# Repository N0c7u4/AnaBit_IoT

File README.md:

# AnaBit IoT

# Wiki

La Wiki de AnaBit es un recurso invaluable que proporciona una amplia gama de información y guías prácticas para aprovechar al máximo esta tarjeta de desarrollo IoT. Al explorar la Wiki, encontraras una gran cantidad de contenido útil y relevante que les permitirá utilizar AnaBit en diversos proyectos. Algunos de los elementos que pueden encontrar en la Wiki incluyen:

-   `Documentación detallada`: La Wiki proporciona una documentación exhaustiva sobre AnaBit, incluyendo especificaciones técnicas, diagramas, esquemas y descripciones de los componentes. Esta información es fundamental para comprender las características y capacidades de la tarjeta.

-   `Guías de configuración`: La Wiki ofrece guías paso a paso para configurar correctamente AnaBit y establecer conexiones con diferentes protocolos de comunicación, como LoRa, Sigfox, Zigbee, WiFi y Bluetooth. Estas guías ayudan a iniciar rápidamente sus proyectos y asegurarse de que la tarjeta esté configurada correctamente.

-   `Tutoriales y ejemplos`: La Wiki contiene tutoriales prácticos que ilustran cómo utilizar AnaBit en diferentes escenarios y aplicaciones. Estos tutoriales incluyen ejemplos de código, configuraciones y diagramas de conexión, lo que facilita la comprensión de los conceptos y el aprendizaje práctico.

-   `Solución de problemas`: En caso de enfrentar dificultades o problemas durante el desarrollo con AnaBit, la Wiki ofrece secciones dedicadas a la resolución de problemas comunes. Estas secciones proporcionan consejos, trucos y posibles soluciones para superar obstáculos técnicos y maximizar la eficiencia en el desarrollo.

-   `Comunidad y recursos adicionales`: Además de la información técnica, la Wiki también puede servir como un punto de encuentro para la comunidad de AnaBit. Se pueden encontrar enlaces a foros de discusión, grupos de usuarios y otros recursos relacionados, lo que permite compartir conocimientos, colaborar e intercambiar ideas con otros entusiastas y expertos en IoT.

la pagina de la Wiki de AnaBit se aloja en el siguiente link:

[Wiki AnaBit](https://anabit-iot.readthedocs.io/es/latest/)

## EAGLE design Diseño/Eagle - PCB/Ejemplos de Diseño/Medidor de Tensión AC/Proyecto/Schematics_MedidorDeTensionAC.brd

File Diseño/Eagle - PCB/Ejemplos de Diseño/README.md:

# Proyectos Ejemplo EAGLE 9.0.0

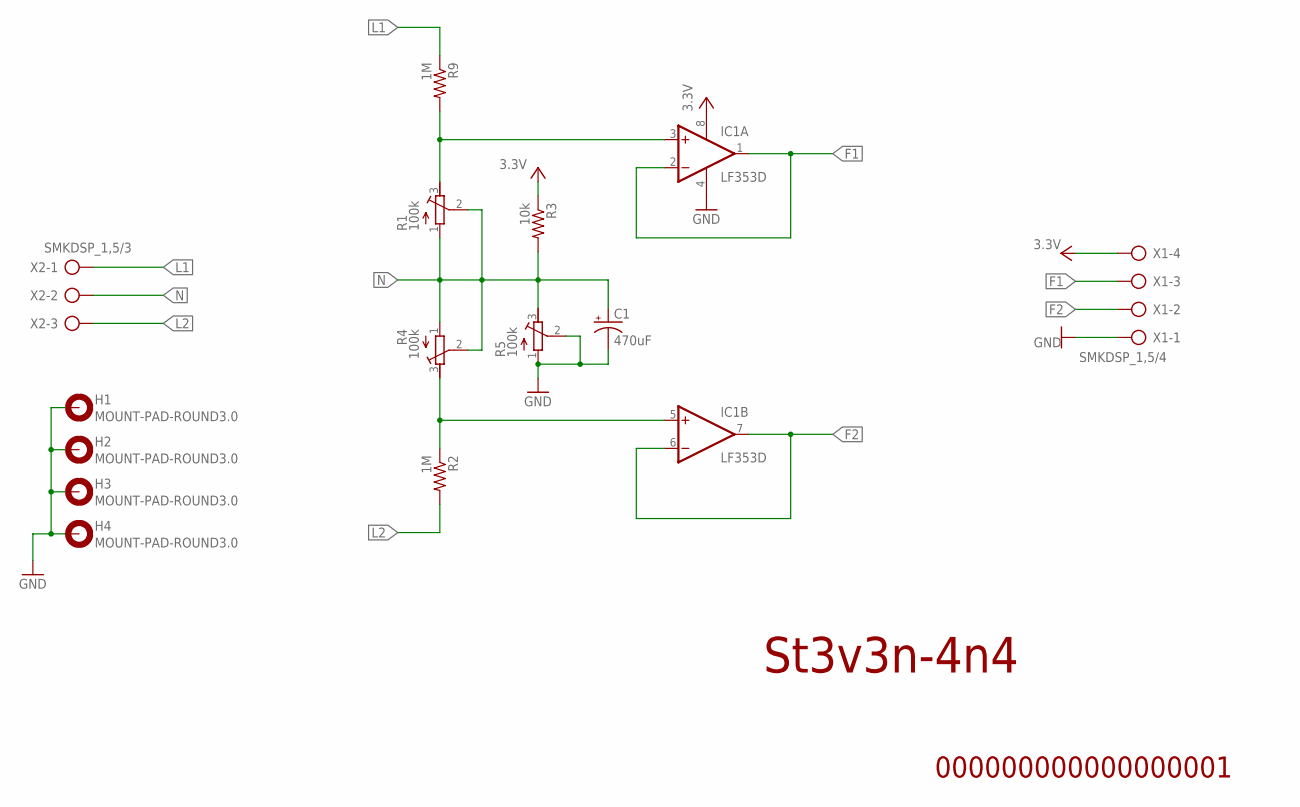
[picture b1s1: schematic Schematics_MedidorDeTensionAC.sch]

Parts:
C1: 470uF; E3,5-8
H1, H2, H3, H4: MOUNT-PAD-ROUND3.0; 3,0-PAD
IC1: LF353D; SO08
R1, R4, R5: 100k; RTRIM64W
R2, R9: 1M; 0207/10
R3: 10k; 0207/10
X1: SMKDSP_1,5/4
X2: SMKDSP_1,5/3

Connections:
F1: IC1.1 (OUT), IC1.2 (-IN), X1.3
F2: IC1.6 (-IN), IC1.7 (OUT), X1.2
GND: C1.-, H1.B3,0, H2.B3,0, H3.B3,0, H4.B3,0, IC1.4 (V-), R5.1 (A), R5.2 (S), X1.1
IN1+: IC1.3 (+IN), R1.3 (E), R9.2
L1: R9.1, X2.1
L2: R2.2, X2.3
N: C1.+, R1.1 (A), R1.2 (S), R3.2, R4.1 (A), R4.2 (S), R5.3 (E), X2.2
unnamed: IC1.5 (+IN), R2.1, R4.3 (E)
VCC: IC1.8 (V+), R3.1, X1.4

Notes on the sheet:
000000000000000001
St3v3n-4n4

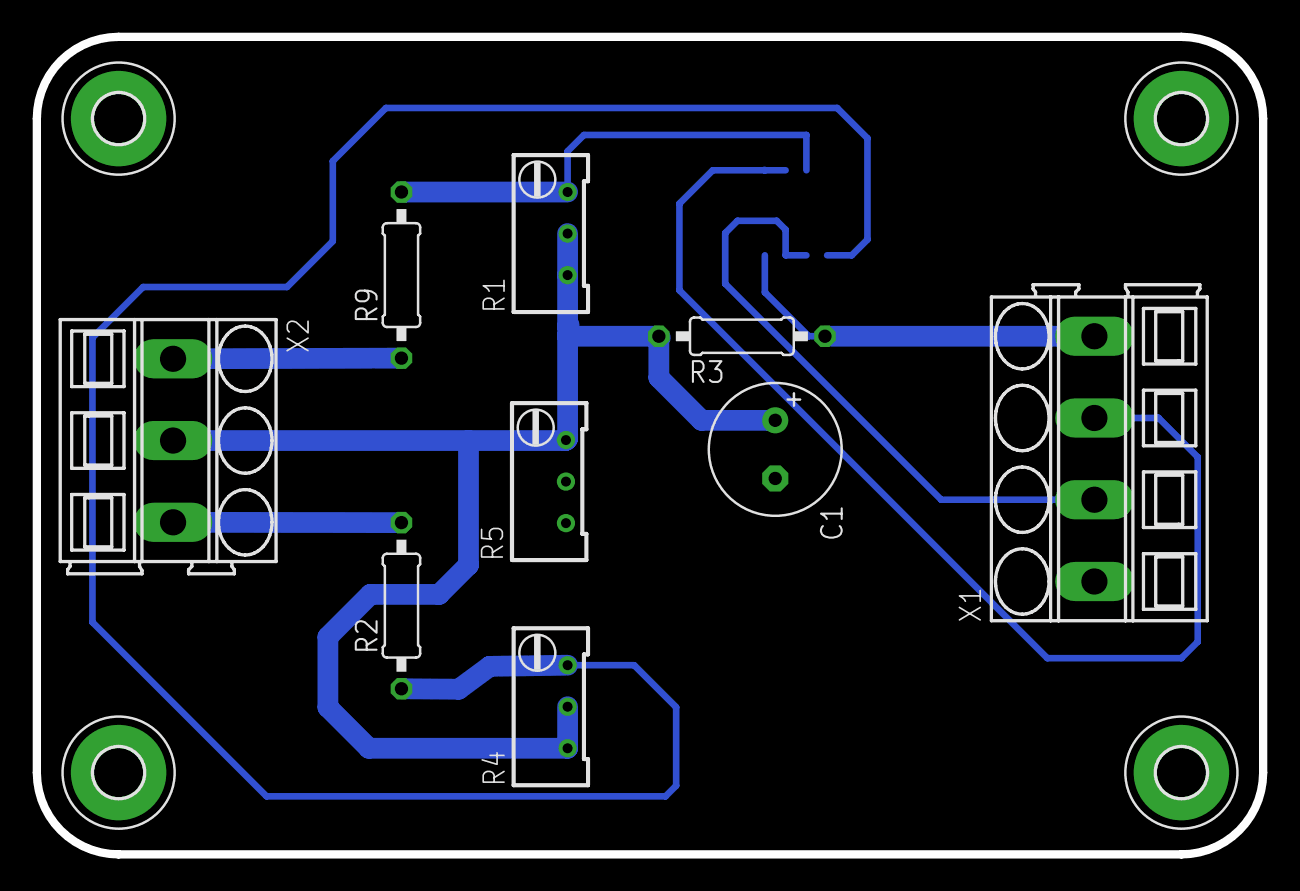
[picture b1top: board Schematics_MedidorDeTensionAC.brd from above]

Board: 2 copper layers, 75.0 x 50.0 mm, 14 parts (1 on the bottom side), 9 nets.

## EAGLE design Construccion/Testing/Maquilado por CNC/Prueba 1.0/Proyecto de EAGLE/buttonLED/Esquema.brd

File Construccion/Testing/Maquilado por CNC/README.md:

# Método de Construcción para PCB

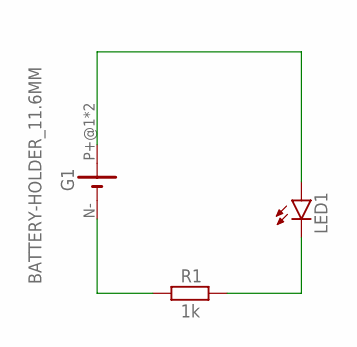
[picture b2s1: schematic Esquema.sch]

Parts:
G1: BATTERY-HOLDER_11.6MM; CELL_RETAINER_11.6MM
LED1: LED5MM
R1: 1k; 0207/10

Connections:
unnamed: G1.N- (-), R1.1
unnamed: LED1.K (C), R1.2
unnamed: G1.P+@1 (+), G1.P+@2 (+), LED1.A

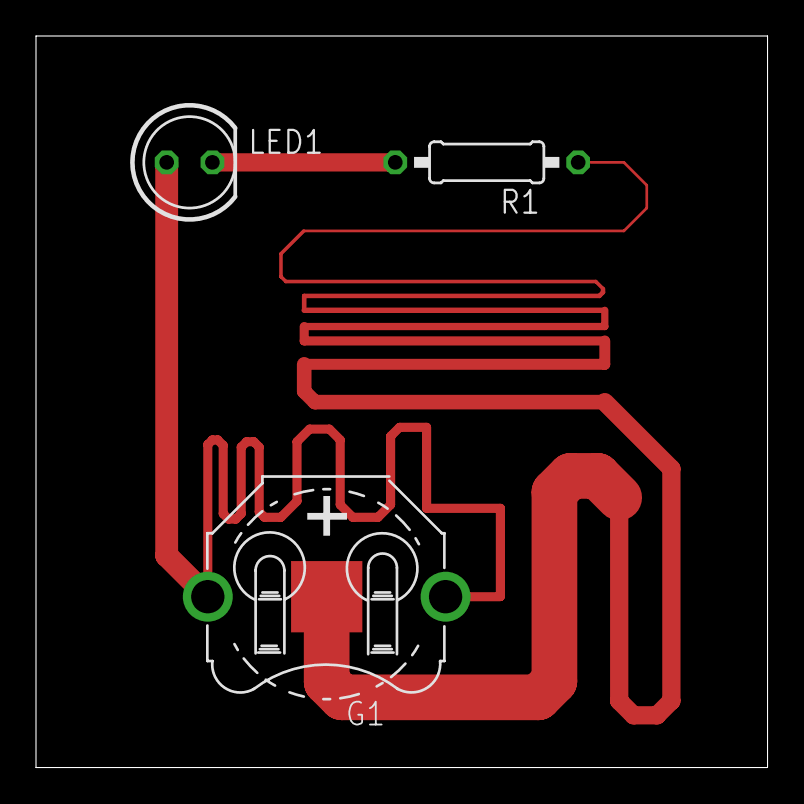
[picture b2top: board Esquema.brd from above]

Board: 2 copper layers, 40.6 x 40.6 mm, 3 parts (0 on the bottom side), 3 nets.

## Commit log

2022-10-15 esp32
2022-10-15 rhf76-052
2022-10-15 rfh76-052
2022-10-15 link
2022-10-21 Agregue un diagrama para la tarjeta de prueba para el RHF76-052 LoraWAN Changes to be committed: new file: Hardware/RHF76-052 - LoraWAN/Datasheet/DisenoDeReferencia.PNG new file: Hardware/RHF76-052 -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
2022-10-21 problemas con nombre de archivos imagen en la documentacion
2022-10-23 Agregue la versione 1.1 de la PCB de prueba para el chip RHF76-052 Changes to be committed: deleted: Hardware/RHF76-052 - LoraWAN/DiagramaCircuital/Backup Of RHF76-052.pdsbak deleted: Hardware/RHF76-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
2022-10-23 Agrege modelo en 3D del modulo RHF76-052 y una imagen del render para el readme principal Changes to be committed: new file: Hardware/RHF76-052 - LoraWAN/.blend/RHF76-052.3ds new file: Hardware/RHF76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
2022-10-23 Cambio de localizacion del archivo de proteus por confusion el PCBv1.0 estaba en el PCBv1.1 y asi visebersa Changes to be committed: modified: Hardware/RHF76-052 - LoraWAN/DiagramaCircuital/PCB_v1.0/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
2022-10-27 Agregue fotos del montaje de PCB_V1.1
2022-10-27 Imagen button copper
2022-10-27 imagen de TTGO con el codigo sender
2022-10-27 Imagen del convertidor TTL a USB con el chip CP2102 y coneccion del montajke PCB con el convertidor
2022-10-27 test hardware lora
2022-11-19 Agregacion de la informacion del sensor que se usara para la medicion de Temperatura presion atmosferica humedad de ambiente para el nodo lora que se utilizara para la tesis
2022-11-19 Se Agrego el algoritmo que se utilizo para el control de TTGO y el sensor de humedad, temperatura, presion atmosferica
2023-01-28 Configuracion del texto para obsidian y agregue la carpeta de construcion agregue en esta ultima la configuracion del software MACH3 Changes to be committed: new file: .img/EsquemaElectronico.PNG.md 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
2023-01-28 modificaciones esteticas del README Changes to be committed: modified: .obsidian/workspace.json modified: Construccion/Maquinado CNC/Motor/README.md
2023-01-28 se elimina carpeta .img puesto que este formato de carpeta no la detecta obsidian Changes to be committed: deleted: .img/EsquemaElectronico.PNG.md
2023-01-28 link del pdf del datasheet del manual del controlador MACH3 Changes to be committed: modified: .obsidian/workspace.json modified: Construccion/Maquinado CNC/Motor/SoftwareMACH3/Manual de uso MACH3.md
2023-01-28 carpetas de testing sin embargo no se ha agragado nada Changes to be committed: modified: .obsidian/app.json modified: .obsidian/workspace.json deleted: Construccion/Maquinado CNC/Motor/Prueba 1.0.md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
2023-01-28 Agregue proyecto de Prueba de Maquilado CNC Changes to be committed: modified: .obsidian/workspace.json new file: Construccion/Testing/Maquilado por CNC/Prueba 1.0/Export EAGLE/copper_top.gbr new fil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
2023-01-28 Estoy en la casa de miguel, ya instale todo estoy probando una configuracion que hice en obsidian en la parte de salto de linea excricto Changes to be committed: modified: .obsidian/app.json modified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
2023-01-28 si se puede ver en previsulizacion si esta bien el salto de linea Changes to be committed: modified: Construccion/Maquinado CNC/Motor/SoftwareMACH3/Manual de uso MACH3.md
2023-01-29 Subi prueba con GIF y tambien subi el instalador de MACH3
2023-01-29 Agregue completa la configuracion del MACH3 con perfiles y hasta la conexion de la sonda
2023-01-29 conexion fisica del sensor de punto zero del eje z Changes to be committed: modified: .obsidian/workspace.json modified: Construccion/Maquinado CNC/Motor/SoftwareMACH3/Manual de uso MACH3.md new file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
2023-01-29 Elimine la carpeta del instalador y deje el archivo complimido Changes to be committed: renamed: Construccion/Maquinado CNC/Motor/SoftwareMACH3/Instalador/SOFTWARE MCH3 USB/MACH3 DEFAULD.rar -> Const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
2023-01-30 Agregue el instalador de EAGLE con licencia y tambien verifique en virus total que no tenga ningun virus... por otro lado hice documentacion de la configuracion basica, mover, rotart y conectar compo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
2023-01-31 Cree un ejemplo de diseño de un modulo de medicion de tension bifasica en EAGLE Changes to be committed: modified: .obsidian/app.json modified: .obsidian/workspace.json new file: "Dise\303\261o/Eagle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
2023-02-01 Codigos G y M aprendiendo y documentando Changes to be committed: modified: .obsidian/app.json modified: .obsidian/workspace.json modified: Construccion/Maquinado CNC/Motor/README.md new file: "Const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
2023-02-03 todo lo de eagle y maquina cnc con el codigo g
2023-02-18 documente la parte 1/5 para la creacion de componentes en eagle nuevos archivos: "Dise\303\261o/Eagle & Fusion360 - PCB/Notas (Crear Componentes - Dise\303\261o Intermedio).md"
2023-02-19 Agregar documentacion de KiCAD
2023-02-19 Instalacion de FreeCAD
2023-02-19 Agregue la documentacion de configuracion basica e instalacion del mismo...
2023-02-20 Comandos de teclado
2023-02-22 Elimine todos los readme puesto que no eran relevantes y agregue algunas cosas de freecad como mas configuraciones de comandos
2023-03-05 se acrego uso del KiCAD y FreeCAD
2023-03-28 pequeños cambios con loRaWAN
2023-03-28 agregue carpeta y estructura de la documentacion del modulo E180-ZG120A de Zigbee EBYTE
2023-03-28 configuracion de obsidian
2023-06-28 iniciando el respositorio
2023-06-29 Capitulo de configuracion de interfaz OTA y configuracion del IDE de Arduino
2023-06-29 se agrego imagenes y modificacion de los titulos con un style agregacion de testing
2023-06-29 modificacion del nombre del codigo de testeo para la microsd
2023-06-29 Se termino el apartado de Testing y configuracion de AnaBit ahora se crean los apartados Ejemplos y Mini Proyectos
2023-06-29 modificacion imagen de la tarjeta AnaBit index.md
2023-06-29 imagen tarjeta AnaBit modificacion
2023-06-29 cambie el nombre de la imagen
2023-06-29 modifique la linea de html a markdown de la imagen
2023-06-30 iniciando el ejemplo de lora
2023-07-01 Se agrego el ejemplo de comunicacion punto a punto de lora con AnaBit
2023-07-03 Ejemplo de comunicacion Zigbee
2023-07-03 modificacion del ejemplo subdivision por titulos
2023-07-04 ultimos retoques
2023-07-04 icono black
2023-07-13 modificacion en maquina CNC
2023-09-17 ultimo comentario
2023-12-14 cambio de nombre de github En la rama master Tu rama está actualizada con 'origin/master'.
    Cambios a ser confirmados:
    modificados: docs/Autor.md
    modificados: docs/Ejemplo_LoRa.md
    modificados: docs/Modo_OTA.md
    modificados: docs/Testing.md
    modificados: docs/index.md
2023-12-14 actualizacion de la pagina web En la rama master Tu rama está actualizada con 'origin/master'.
    Cambios a ser confirmados:
    modificados: .readthedocs.yaml
